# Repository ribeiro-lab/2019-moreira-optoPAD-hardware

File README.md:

# optoPAD-hardware

Hardware schematics and layouts for main and LED board of the optoPAD (Moreira et al., 2019). The files have been created using Autodesk EAGLE electronic design automation (https://www.autodesk.com/products/eagle/overview) software.

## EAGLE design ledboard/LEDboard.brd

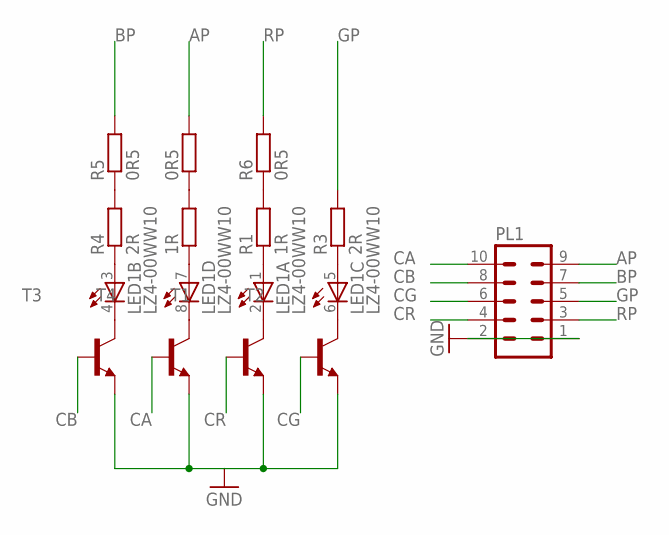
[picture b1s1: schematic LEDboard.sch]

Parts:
0R5: R-EU_R0805; R0805
1R: R-EU_R1210; R1210
LED1: LZ4-00WW10
PL1: 10V
R1: 1R; R1210
R3, R4: 2R; R2512
R5, R6: 0R5; R0805
T1, T2, T3, T4: PZT2222A-NPN-SOT223; SOT223

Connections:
AP: 0R5.2, PL1.9
BP: PL1.7, R5.2
CA: PL1.10, T4.1 (B)
CB: PL1.8, T3.1 (B)
CG: PL1.6, T2.1 (B)
CR: PL1.4, T1.1 (B)
GND: PL1.1, PL1.2, T1.3 (E), T2.3 (E), T3.3 (E), T4.3 (E)
GP: PL1.5, R3.2
unnamed: LED1.1 (A), R1.1
unnamed: 1R.1, LED1.7 (A)
unnamed: LED1.5 (A), R3.1
unnamed: LED1.3 (A), R4.1
unnamed: R4.2, R5.1
unnamed: R1.2, R6.1
unnamed: 0R5.1, 1R.2
unnamed: LED1.2 (C), T1.4 (C)
unnamed: LED1.6 (C), T2.4 (C)
unnamed: LED1.4 (C), T3.4 (C)
unnamed: LED1.8 (C), T4.4 (C)
RP: PL1.3, R6.2

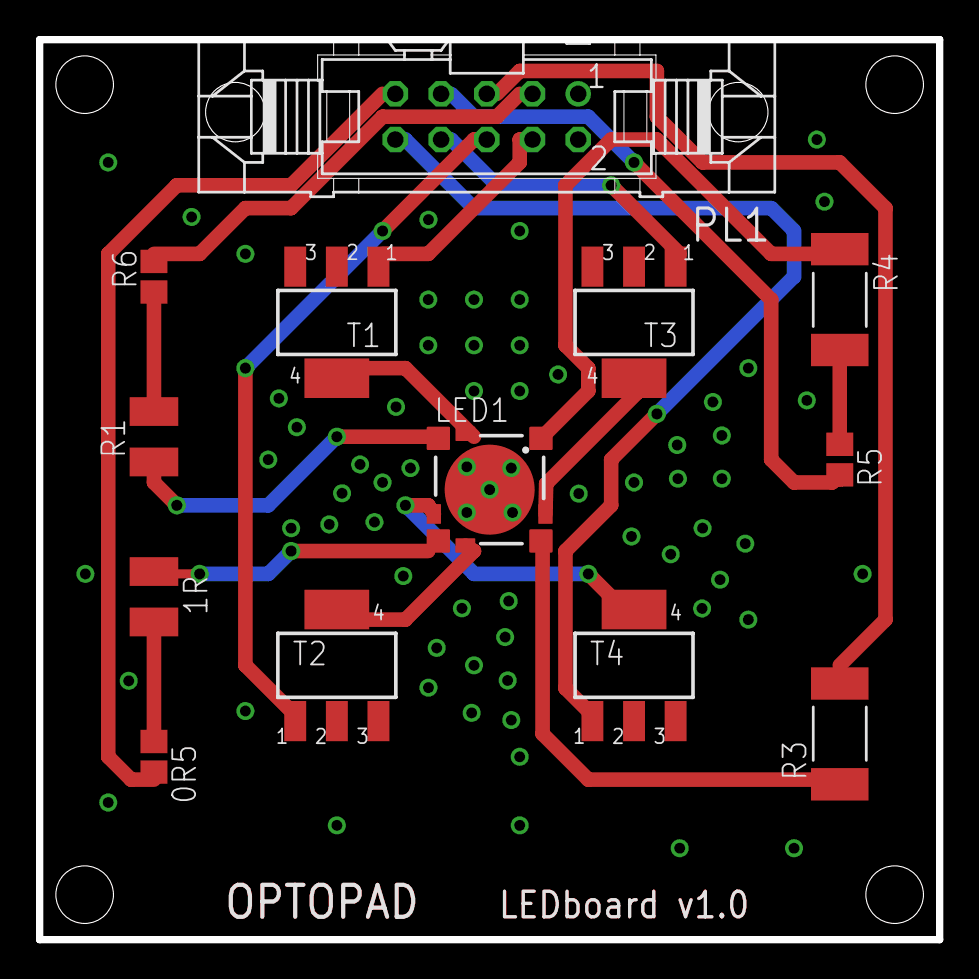
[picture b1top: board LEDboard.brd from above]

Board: 2 copper layers, 50.0 x 50.0 mm, 13 parts (0 on the bottom side), 20 nets.

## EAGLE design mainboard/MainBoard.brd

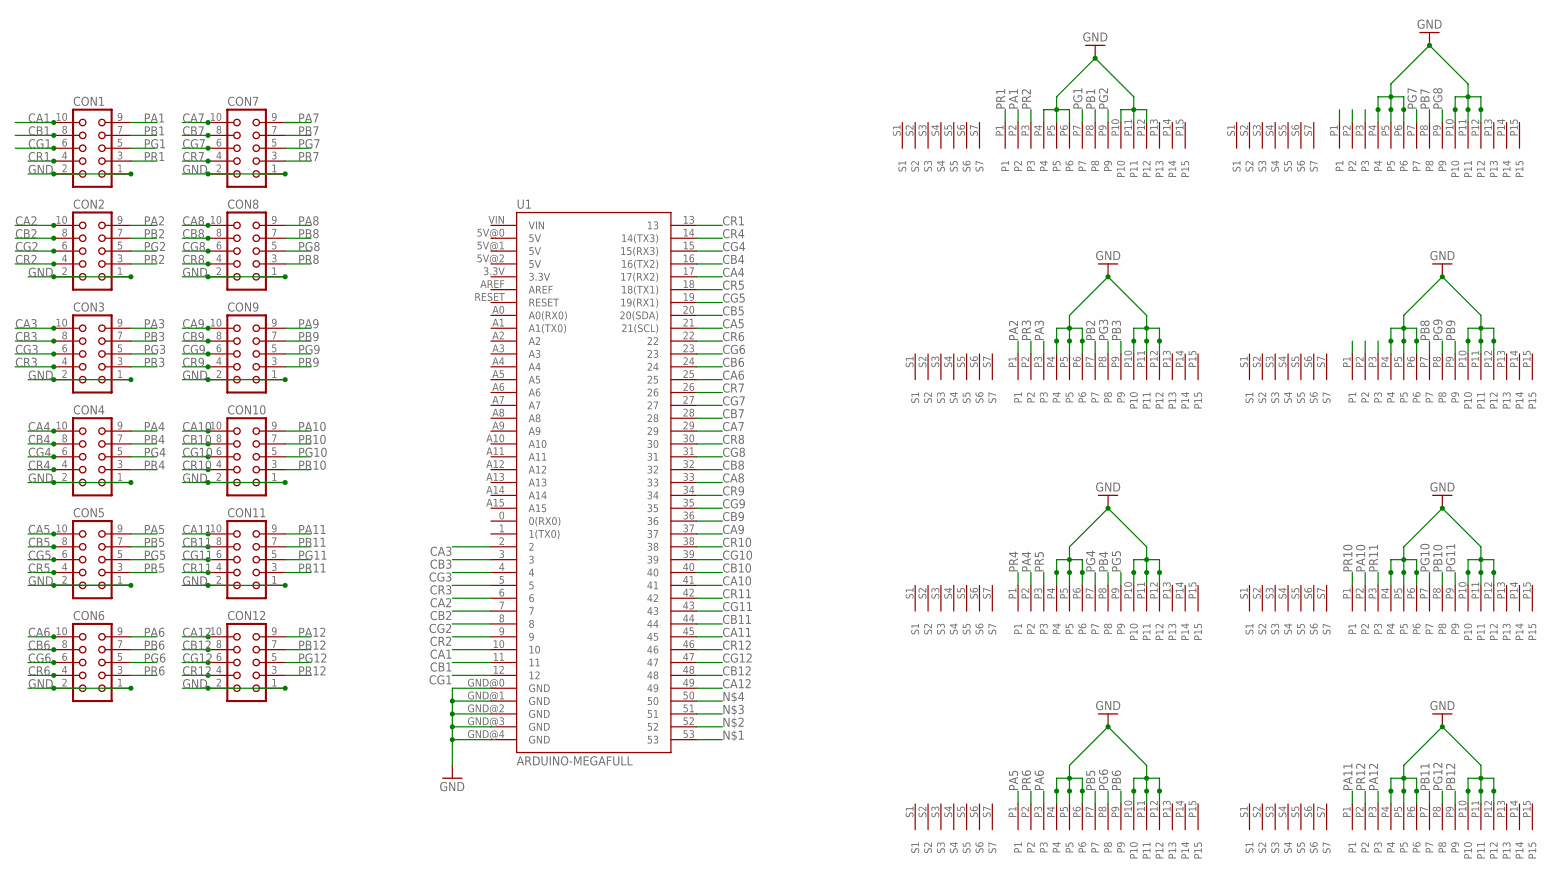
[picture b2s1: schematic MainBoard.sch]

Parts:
CON1, CON2, CON3, CON4, CON5, CON6, CON7, CON8, CON9, CON10, CON11, CON12: CON10
P1: 87779-1001
U1: ARDUINO-MEGAFULL; ARDUINO_MEGA
U$2, U$3, U$4, U$5, U$6, U$7, U$8: 87779-1001

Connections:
CA1: CON1.10, U1.10
CA2: CON2.10, U1.6
CA3: CON3.10, U1.2
CA4: CON4.10, U1.17 (17(RX2))
CA5: CON5.10, U1.21 (21(SCL))
CA6: CON6.10, U1.25
CA7: CON7.10, U1.29
CA8: CON8.10, U1.33
CA9: CON9.10, U1.37
CA10: CON10.10, U1.41
CA11: CON11.10, U1.45
CA12: CON12.10, U1.49
CB1: CON1.8, U1.11
CB2: CON2.8, U1.7
CB3: CON3.8, U1.3
CB4: CON4.8, U1.16 (16(TX2))
CB5: CON5.8, U1.20 (20(SDA))
CB6: CON6.8, U1.24
CB7: CON7.8, U1.28
CB8: CON8.8, U1.32
CB9: CON9.8, U1.36
CB10: CON10.8, U1.40
CB11: CON11.8, U1.44
CB12: CON12.8, U1.48
CG1: CON1.6, U1.12
CG2: CON2.6, U1.8
CG3: CON3.6, U1.4
CG4: CON4.6, U1.15 (15(RX3))
CG5: CON5.6, U1.19 (19(RX1))
CG6: CON6.6, U1.23
CG7: CON7.6, U1.27
CG8: CON8.6, U1.31
CG9: CON9.6, U1.35
CG10: CON10.6, U1.39
CG11: CON11.6, U1.43
CG12: CON12.6, U1.47
CR1: CON1.4, U1.13
CR2: CON2.4, U1.9
CR3: CON3.4, U1.5
CR4: CON4.4, U1.14 (14(TX3))
CR5: CON5.4, U1.18 (18(TX1))
CR6: CON6.4, U1.22
CR7: CON7.4, U1.26
CR8: CON8.4, U1.30
CR9: CON9.4, U1.34
CR10: CON10.4, U1.38
CR11: CON11.4, U1.42
CR12: CON12.4, U1.46
GND: CON1.1, CON1.2, CON2.1, CON2.2, CON3.1, CON3.2, CON4.1, CON4.2, CON5.1, CON5.2, CON6.1, CON6.2, CON7.1, CON7.2, CON8.1, CON8.2, CON9.1, CON9.2, CON10.1, CON10.2, CON11.1, CON11.2, CON12.1, CON12.2, P1.P4, P1.P5, P1.P6, P1.P10, P1.P11, P1.P12, U1.GND@0 (GND), U1.GND@1 (GND), U1.GND@2 (GND), U1.GND@3 (GND), U1.GND@4 (GND), U$2.P4, U$2.P5, U$2.P6, U$2.P10, U$2.P11, U$2.P12, U$3.P4, U$3.P5, U$3.P6, U$3.P10, U$3.P11, U$3.P12, U$4.P4, U$4.P5, U$4.P6, U$4.P10, U$4.P11, U$4.P12, U$5.P4, U$5.P5, U$5.P6, U$5.P10, U$5.P11, U$5.P12, U$6.P4, U$6.P5, U$6.P6, U$6.P10, U$6.P11, U$6.P12, U$7.P4, U$7.P5, U$7.P6, U$7.P10, U$7.P11, U$7.P12, U$8.P4, U$8.P5, U$8.P6, U$8.P10, U$8.P11, U$8.P12
PA1: CON1.9, P1.P2
PA2: CON2.9, U$2.P1
PA3: CON3.9, U$2.P3
PA4: CON4.9, U$3.P2
PA5: CON5.9, U$4.P1
PA6: CON6.9, U$4.P3
PA7: CON7.9, U$5.P2
PA8: CON8.9, U$6.P1
PA9: CON9.9, U$6.P3
PA10: CON10.9, U$7.P2
PA11: CON11.9, U$8.P1
PA12: CON12.9, U$8.P3
PB1: CON1.7, P1.P8
PB2: CON2.7, U$2.P7
PB3: CON3.7, U$2.P9
PB4: CON4.7, U$3.P8
PB5: CON5.7, U$4.P7
PB6: CON6.7, U$4.P9
PB7: CON7.7, U$5.P8
PB8: CON8.7, U$6.P7
PB9: CON9.7, U$6.P9
PB10: CON10.7, U$7.P8
PB11: CON11.7, U$8.P7
PB12: CON12.7, U$8.P9
PG1: CON1.5, P1.P7
PG2: CON2.5, P1.P9
PG3: CON3.5, U$2.P8
PG4: CON4.5, U$3.P7
PG5: CON5.5, U$3.P9
PG6: CON6.5, U$4.P8
PG7: CON7.5, U$5.P7
PG8: CON8.5, U$5.P9
PG9: CON9.5, U$6.P8
PG10: CON10.5, U$7.P7
PG11: CON11.5, U$7.P9
PG12: CON12.5, U$8.P8
PR1: CON1.3, P1.P1
PR2: CON2.3, P1.P3
PR3: CON3.3, U$2.P2
PR4: CON4.3, U$3.P1
PR5: CON5.3, U$3.P3
PR6: CON6.3, U$4.P2
PR7: CON7.3, U$5.P1
PR8: CON8.3, U$5.P3
PR9: CON9.3, U$6.P2
PR10: CON10.3, U$7.P1
PR11: CON11.3, U$7.P3
PR12: CON12.3, U$8.P2

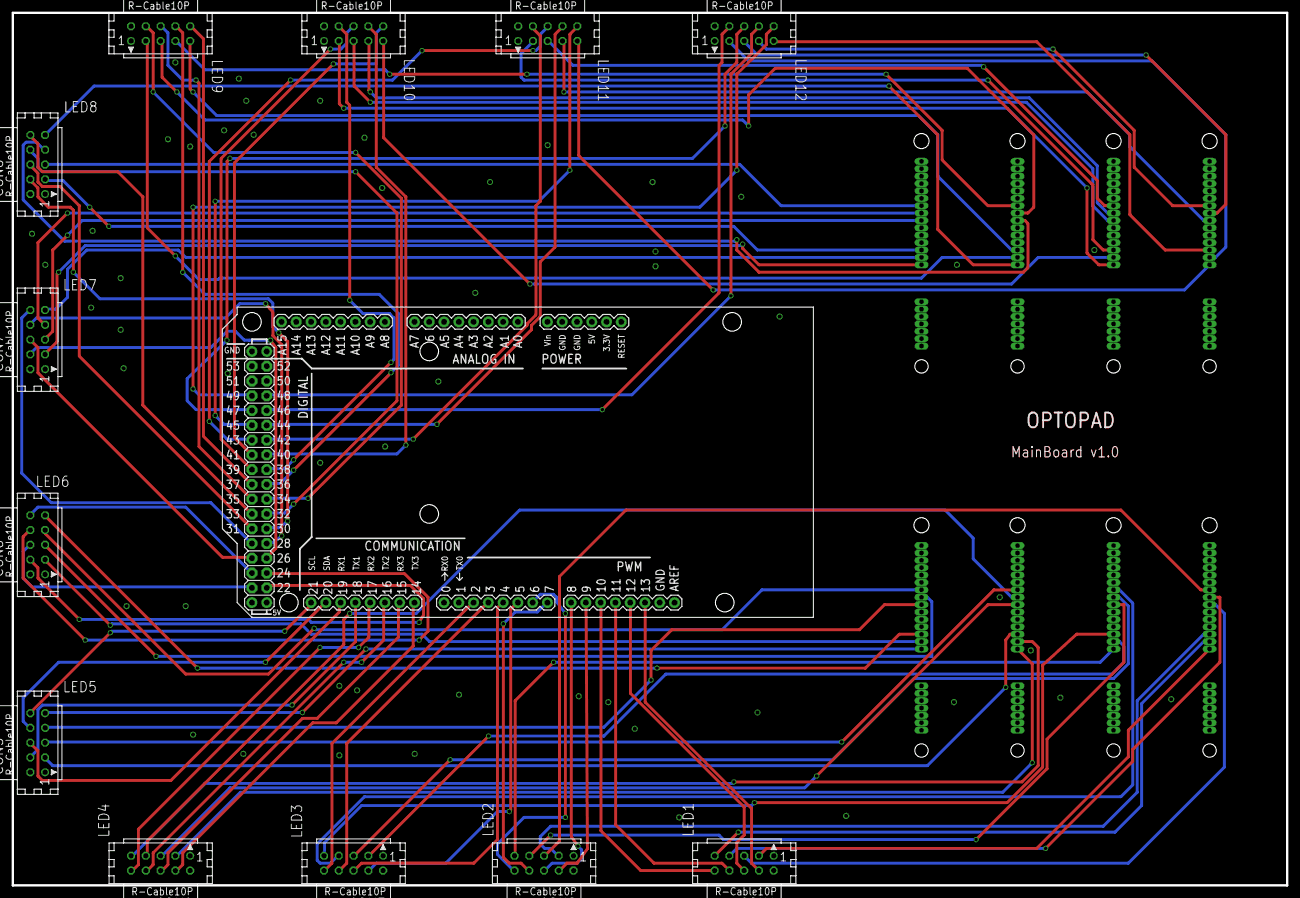
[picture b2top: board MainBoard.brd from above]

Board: 2 copper layers, 219.1 x 150.0 mm, 21 parts (0 on the bottom side), 97 nets.

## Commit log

2018-11-19 schematics uploaded with production notes

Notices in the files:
parts and their libraries:
SparkFun-Boards: Licensing: CC v3.0 Share-Alike You are welcome to use this library for commercial purposes.
